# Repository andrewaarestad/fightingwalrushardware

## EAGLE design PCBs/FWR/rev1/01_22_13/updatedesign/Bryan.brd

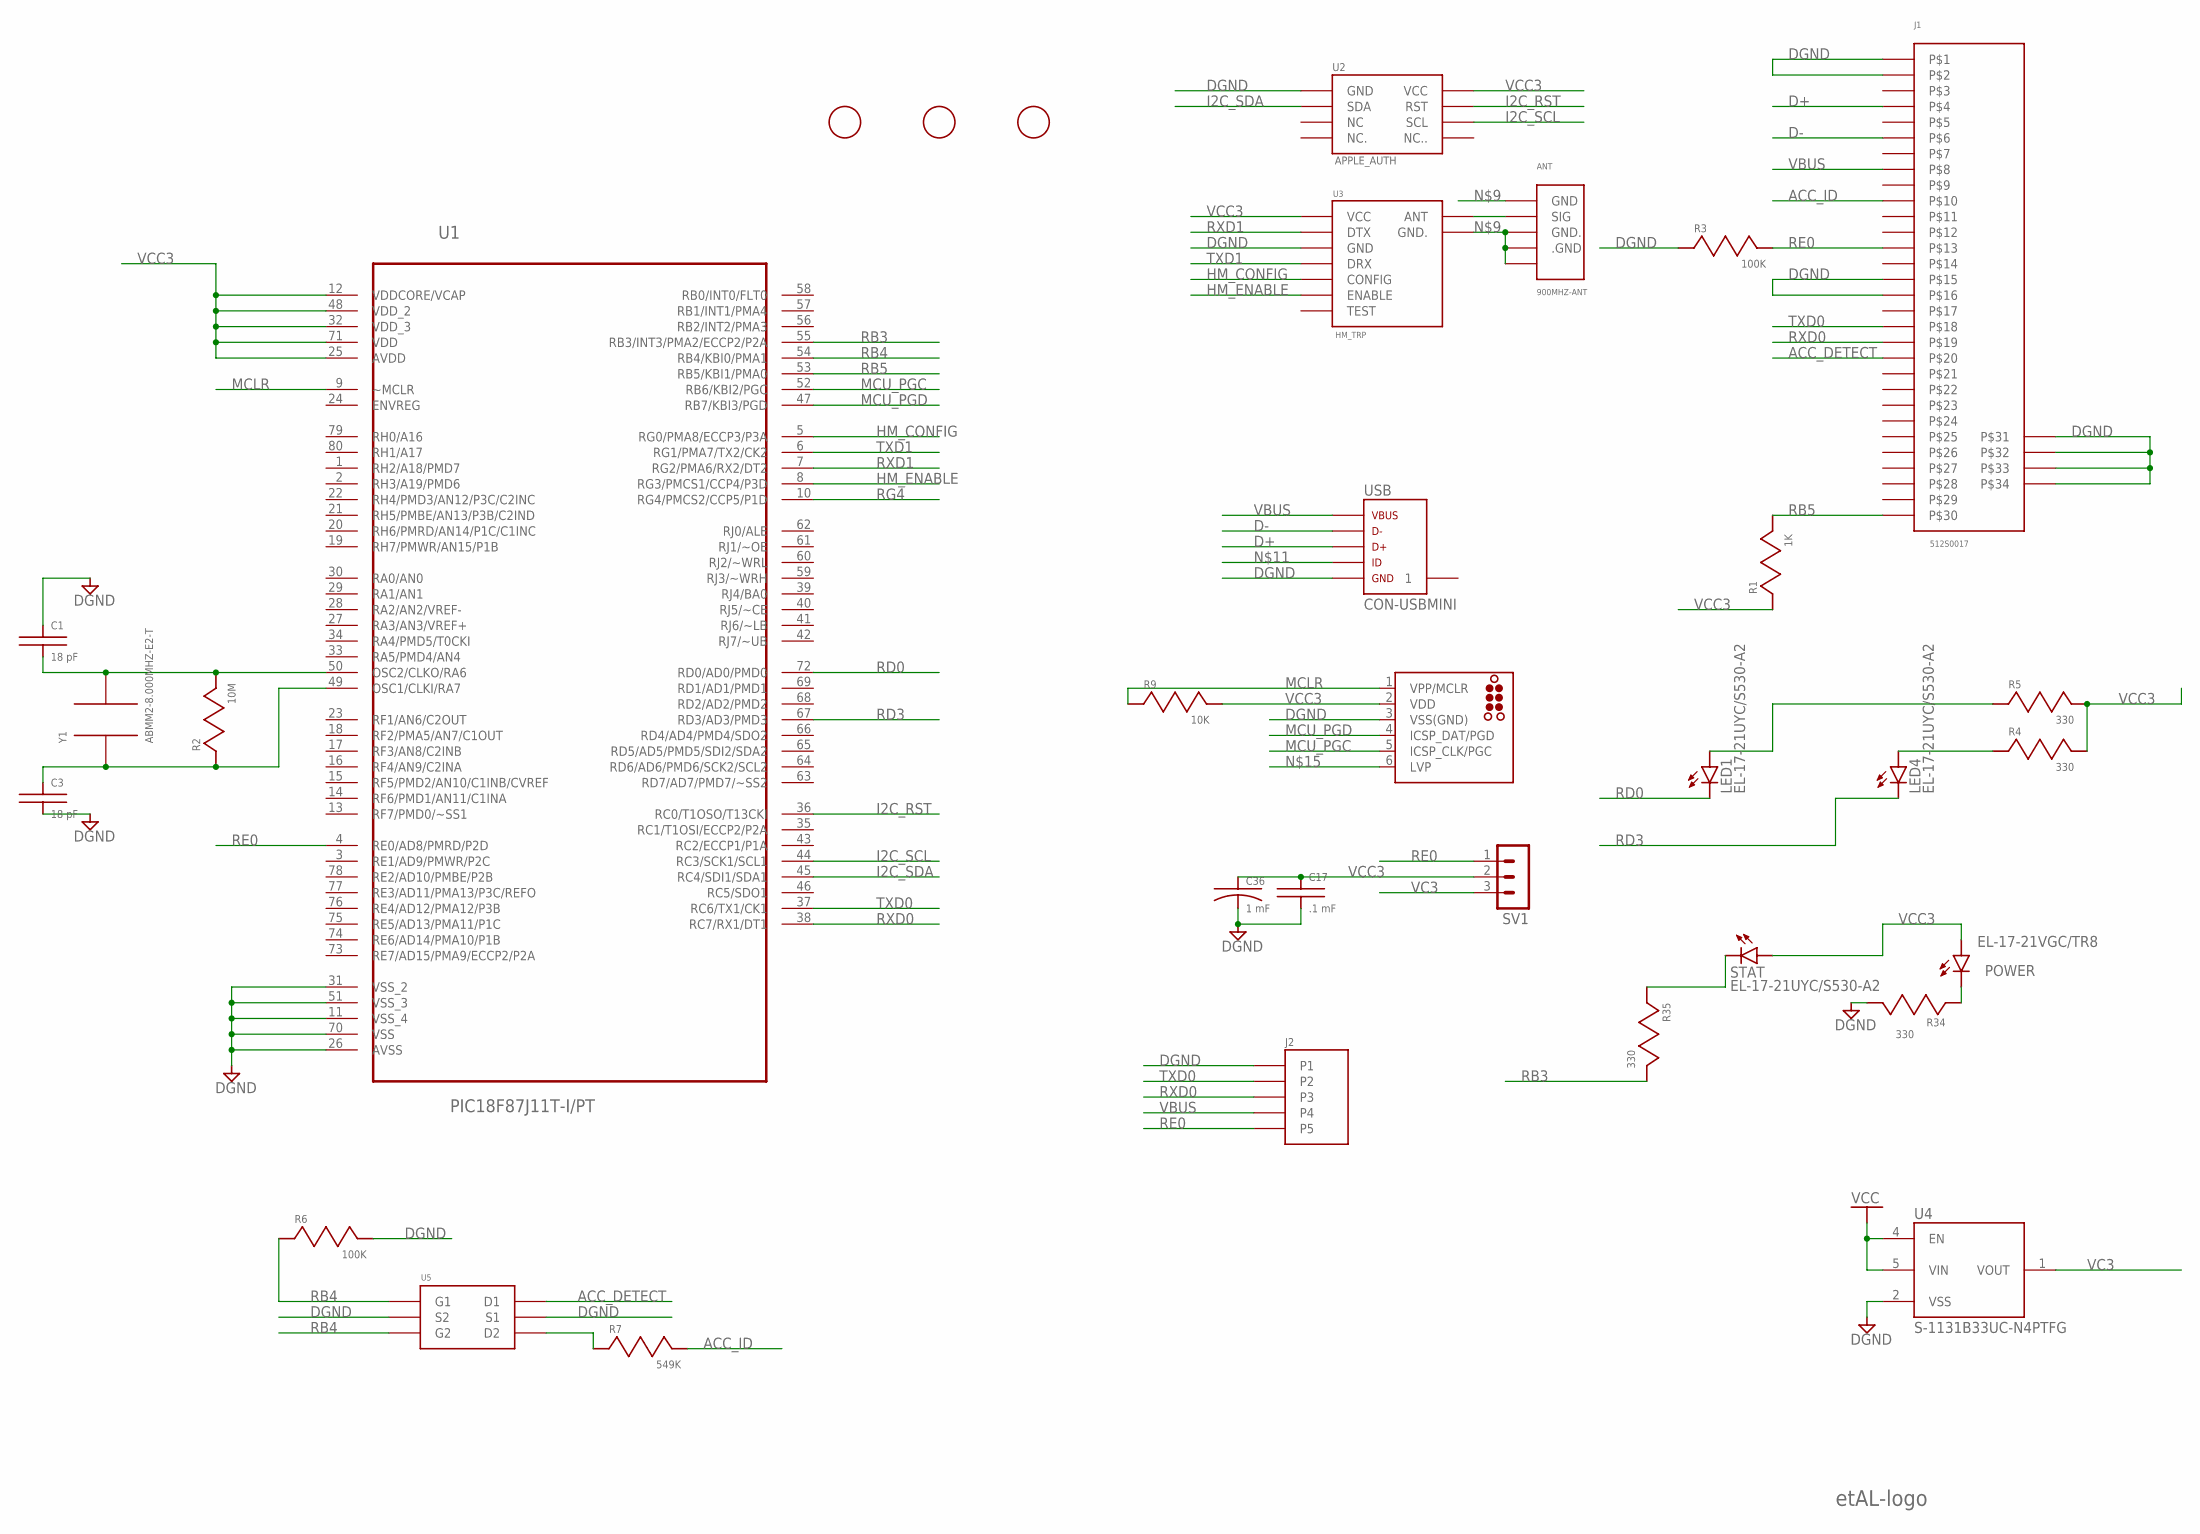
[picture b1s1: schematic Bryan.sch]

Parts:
ANT: 900MHZ-ANT
C1, C3: 18 pF; 0603
C17: .1 mF; 0603
C36: 1 mF; 1206-LONG
J1: 512S0017
J2: LIGHTNING_C11
J3: TC2030-MCP
LED1, LED4: EL-17-21UYC/S530-A2; DIODE-0804
POWER: EL-17-21VGC/TR8; DIODE-0804
R1: 1K; 0603
R2: 10M; 0603
R3, R6: 100K; 0603
R4, R5, R34, R35: 330; 0603
R7: 549K; 0603
R9: 10K; 0603
STAT: EL-17-21UYC/S530-A2; DIODE-0804
SV1: MA03-1
U1: PIC18F87J11T-I/PT; QFP50P1400X1400X120-80N
U2: APPLE_AUTH
U3: HM_TRP; HM-TRP
U4: S-1131B33UC-N4PTFG; SOT-89-5
U5: FDC6301N; SUPER_SOT_6
U$1, U$3, U$4: FIDUCIAL
U$2: ETAL-LOGO
USB: CON-USBMINI; USBMINI
Y1: ABMM2-8.000MHZ-E2-T; CRYSTAL-6X3

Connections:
ACC_DETECT: J1.P$20, U5.P$6 (D1)
ACC_ID: J1.P$10, R7.2
D+: J1.P$4, USB.D+
D-: J1.P$6, USB.D-
DGND: C1.1, C3.2, C17.2, C36.1 (ANODE), J1.P$1, J1.P$2, J1.P$15, J1.P$16, J1.P$31, J1.P$32, J1.P$33, J1.P$34, J2.P1, J3.3 (VSS(GND)), R3.1, R6.2, R34.2, U1.11 (VSS_4), U1.26 (AVSS), U1.31 (VSS_2), U1.51 (VSS_3), U1.70 (VSS), U2.P$1 (GND), U3.P3 (GND), U4.2 (VSS), U5.P$2 (S2), U5.P$5 (S1), USB.GND
HM_CONFIG: U1.5 (RG0/PMA8/ECCP3/P3A), U3.P5 (CONFIG)
HM_ENABLE: U1.8 (RG3/PMCS1/CCP4/P3D), U3.P6 (ENABLE)
I2C_RST: U1.36 (RC0/T1OSO/T13CKI), U2.P$7 (RST)
I2C_SCL: U1.44 (RC3/SCK1/SCL1), U2.P$6 (SCL)
I2C_SDA: U1.45 (RC4/SDI1/SDA1), U2.P$2 (SDA)
MCLR: J3.1 (VPP/MCLR), R9.1, U1.9 (~MCLR)
MCU_PGC: J3.5 (ICSP_CLK/PGC), U1.52 (RB6/KBI2/PGC)
MCU_PGD: J3.4 (ICSP_DAT/PGD), U1.47 (RB7/KBI3/PGD)
unnamed: ANT.P$2 (SIG), U3.P9 (ANT)
unnamed: C1.2, R2.2, U1.50 (OSC2/CLKO/RA6), Y1.P$3 (2)
unnamed: LED1.CATHODE, R5.1
unnamed: C3.1, R2.1, U1.49 (OSC1/CLKI/RA7), Y1.P$1 (1)
unnamed: R35.1, STAT.ANODE
unnamed: LED4.CATHODE, R4.1
unnamed: R7.1, U5.P$4 (D2)
unnamed: POWER.ANODE, R34.1
unnamed: ANT.P$1 (.GND), ANT.P$3 (GND.), ANT.P$4 (GND), ANT.P$5, U3.P8 (GND.)
RB3: R35.2, U1.55 (RB3/INT3/PMA2/ECCP2/P2A)
RB4: R6.1, U1.54 (RB4/KBI0/PMA1), U5.P$1 (G1), U5.P$3 (G2)
RB5: J1.P$30, R1.2, U1.53 (RB5/KBI1/PMA0)
RD0: LED1.ANODE, U1.72 (RD0/AD0/PMD0)
RD3: LED4.ANODE, U1.67 (RD3/AD3/PMD3)
RE0: J1.P$13, J2.P5, R3.2, SV1.1, U1.4 (RE0/AD8/PMRD/P2D)
RG4: U1.10 (RG4/PMCS2/CCP5/P1D)
RXD0: J1.P$19, J2.P3, U1.38 (RC7/RX1/DT1)
RXD1: U1.7 (RG2/PMA6/RX2/DT2), U3.P2 (DTX)
TXD0: J1.P$18, J2.P2, U1.37 (RC6/TX1/CK1)
TXD1: U1.6 (RG1/PMA7/TX2/CK2), U3.P4 (DRX)
VBUS: J1.P$8, J2.P4, USB.VBUS
VC3: SV1.3, U4.1 (VOUT)
VCC: U4.4 (EN), U4.5 (VIN)
VCC3: C17.1, C36.2 (CATHODE), J3.2 (VDD), POWER.CATHODE, R1.1, R4.2, R5.2, R9.2, STAT.CATHODE, SV1.2, U1.12 (VDDCORE/VCAP), U1.25 (AVDD), U1.32 (VDD_3), U1.48 (VDD_2), U1.71 (VDD), U2.P$8 (VCC), U3.P1 (VCC)

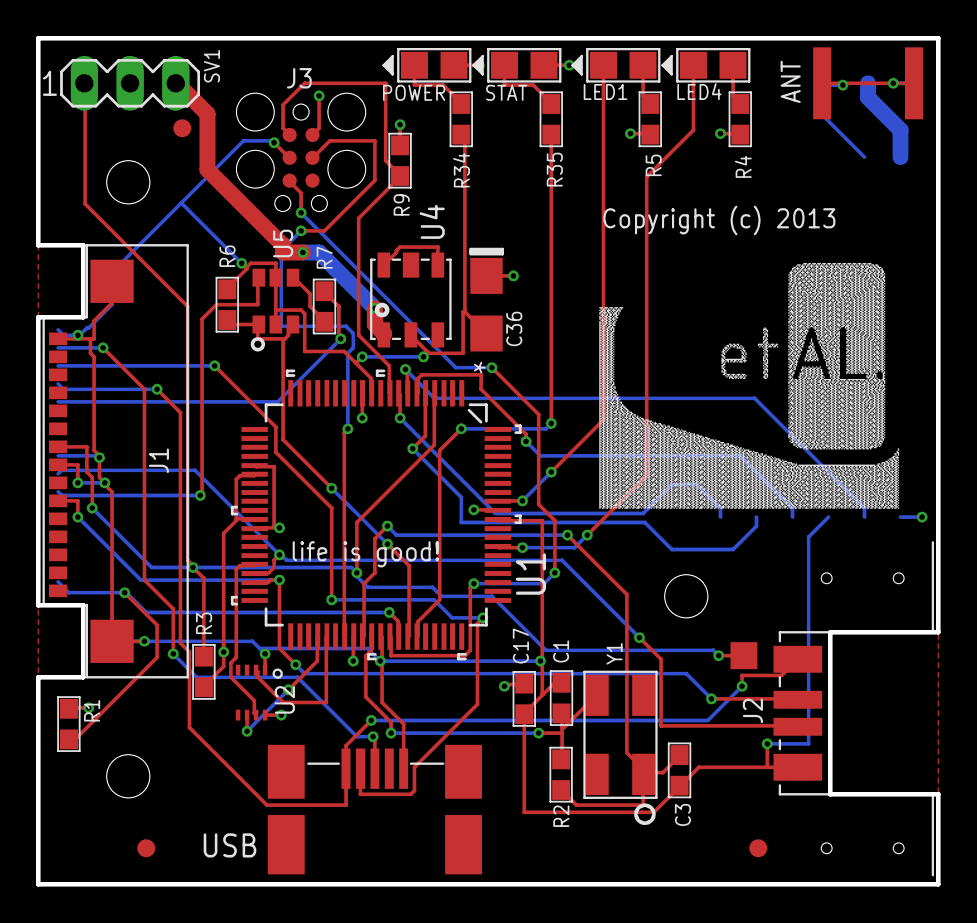
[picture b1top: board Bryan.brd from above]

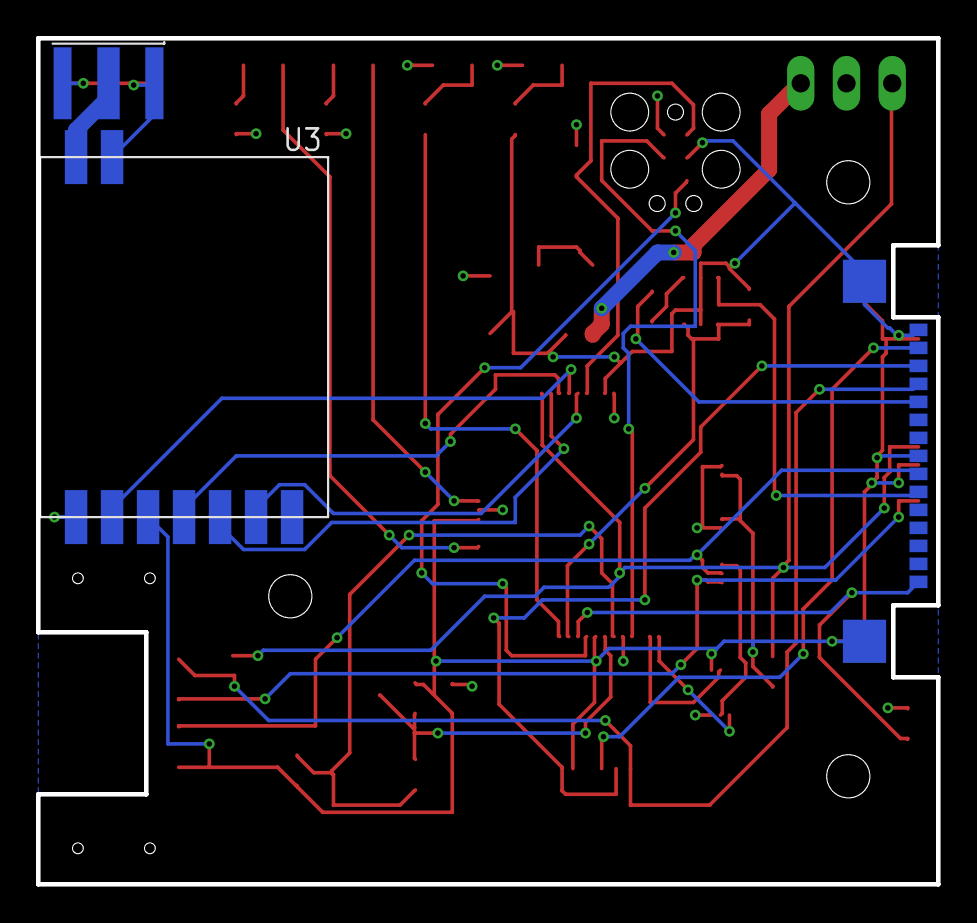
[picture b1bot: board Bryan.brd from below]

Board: 4 copper layers, 50.0 x 47.0 mm, 34 parts (2 on the bottom side), 36 nets.

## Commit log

2013-03-30 initial import of PCB data
2013-03-30 add FWR rev2 initial schematic
2013-04-05 add new files
2013-04-05 moved files
2013-04-05 created eagle project for rev2
2013-04-05 renamed to lib
2013-04-05 rev2 changes to FWR schematic

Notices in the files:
PCBs/FWR/rev1/01_22_13/updatedesign/Bryan.brd:
Copyright (c) 2013
parts and their libraries:
BrandWatch: ©2009 ROFA.cz
